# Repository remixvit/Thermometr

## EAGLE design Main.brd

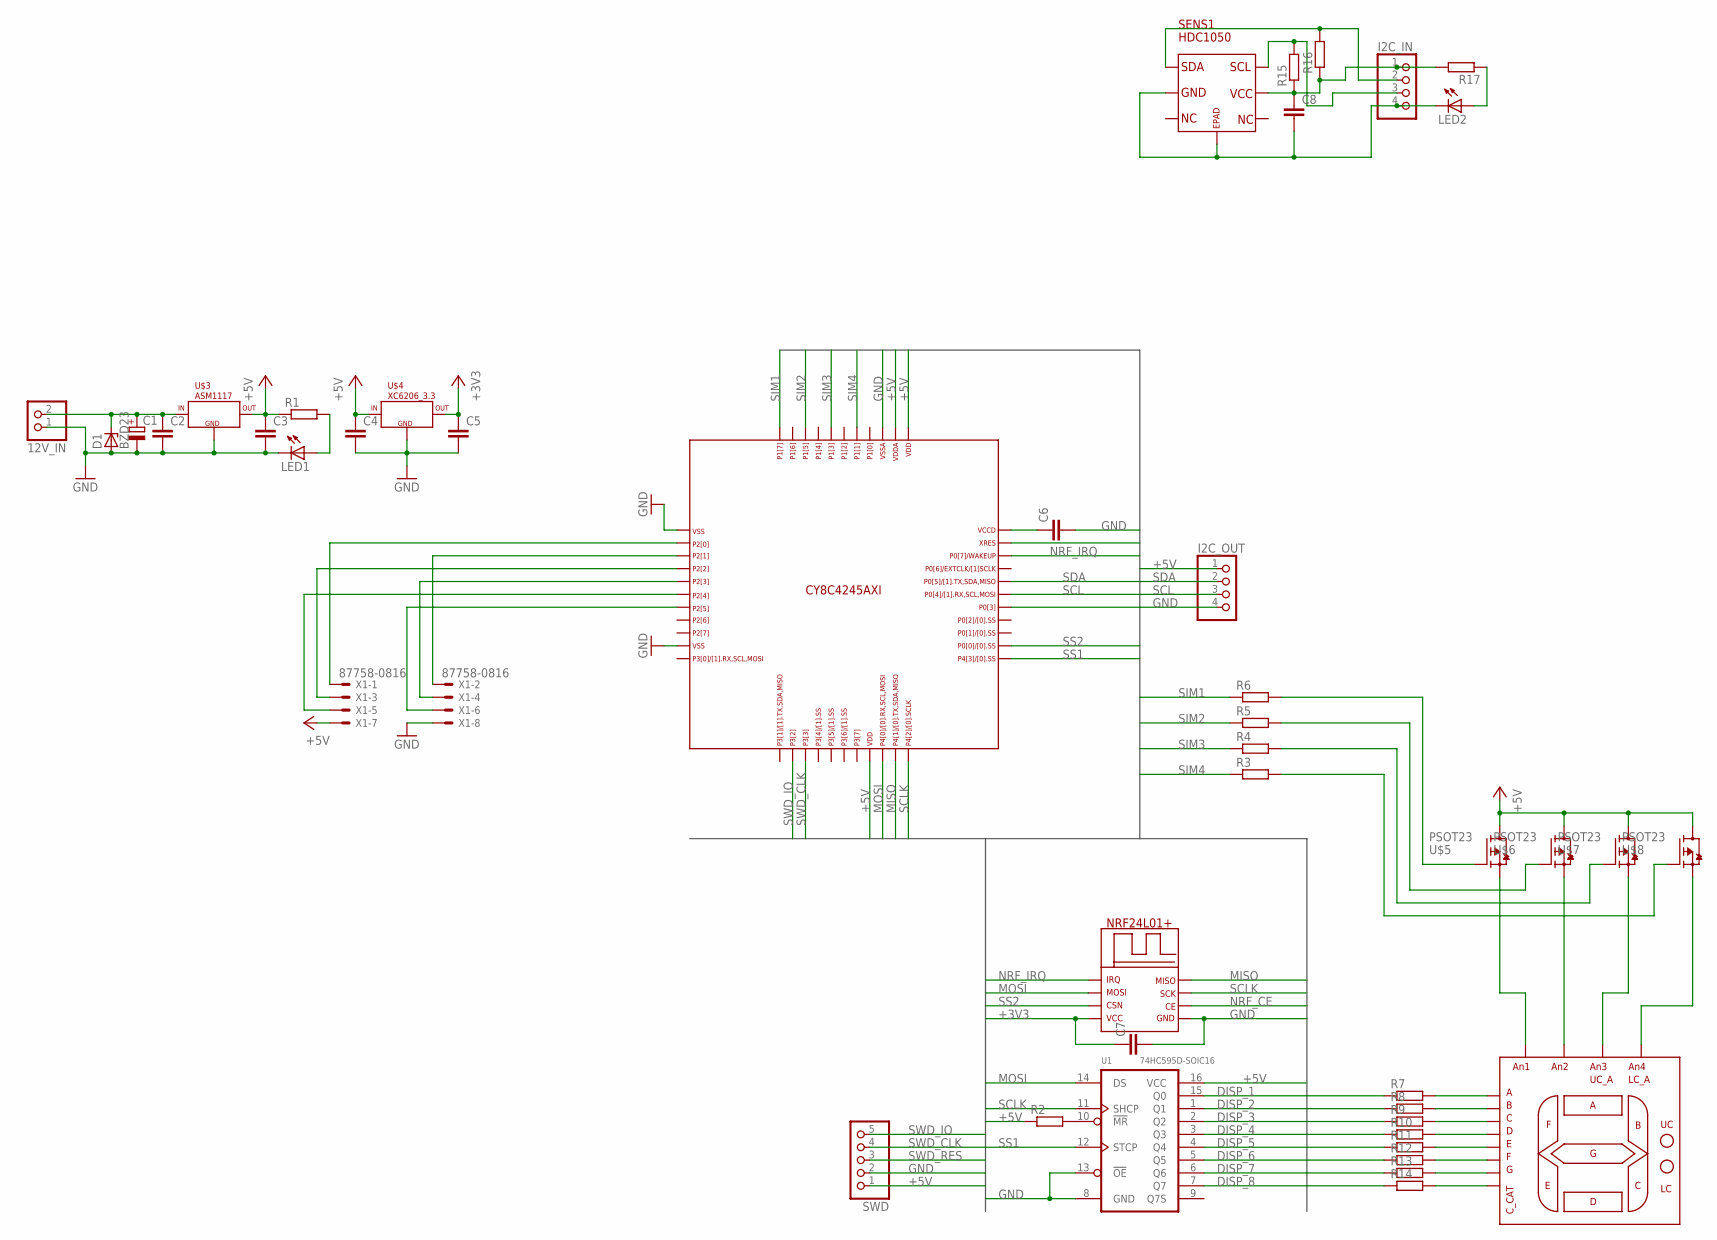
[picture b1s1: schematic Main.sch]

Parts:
12V_IN: PINHD-1X2; 1X02
C1: CPOL-EU150CLZ-0810; 150CLZ-0810
C2, C3, C4, C5, C6, C7, C8: C-EUC0805; C0805
D1: BZD23; SOD81
DISPLAY1: 4DIGIT_7SEG; 4DIG_7SEG_5.3X19
I2C_IN, I2C_OUT: PINHD-1X4; 1X04
LED1, LED2: LEDCHIP-LED0805; CHIP-LED0805
R1, R2, R3, R4, R5, R6, R7, R8, R9, R10, R11, R12, R13, R14, R15, R16, R17: R-EU_M0805; M0805
SENS1: HDC1050; PWSON6
SWD: PINHD-1X5; 1X05
U1: 74HC595D-SOIC16; SOIC16-1.27-10X3.9MM
U$1: CY8C4245; TQFP44_CY_LOGO
U$2: NRF24; NRF
U$3: ASM1117; SOT223
U$4: XC6206_3.3; SOT23
U$5, U$6, U$7, U$8: PSOT23; SOT23
X1: 87758-0816

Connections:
+3V3: C5.1, C7.1, U$2.VCC, U$4.2 (OUT)
+5V: C3.1, C4.1, I2C_OUT.1, R1.1, R2.1, SWD.1, U1.16 (VCC), U$1.19, U$1.34, U$1.35, U$3.2 (OUT), U$3.4 (OUT), U$4.3 (IN), U$5.S, U$6.S, U$7.S, U$8.S, X1.7
DISP_1: R7.1, U1.15 (Q0)
DISP_2: R8.1, U1.1 (Q1)
DISP_3: R9.1, U1.2 (Q2)
DISP_4: R10.1, U1.3 (Q3)
DISP_5: R11.1, U1.4 (Q4)
DISP_6: R12.1, U1.5 (Q5)
DISP_7: R13.1, U1.6 (Q6)
DISP_8: R14.1, U1.7 (Q7)
GND: 12V_IN.1, C1.-, C2.2, C3.2, C4.2, C5.2, C6.2, C7.2, D1.A, I2C_OUT.4, LED1.C, SWD.2, U1.8 (GND), U1.13 (!OE), U$1.1, U$1.10, U$1.36, U$2.GND, U$3.1 (GND), U$4.1 (GND), X1.8
MISO: U$1.21, U$2.MISO
MOSI: U1.14 (DS), U$1.20, U$2.MOSI
unnamed: 12V_IN.2, C1.+, C2.1, D1.C, U$3.3 (IN)
unnamed: R2.2, U1.10 (!MR)
unnamed: LED1.A, R1.2
unnamed: C8.1, I2C_IN.1, R15.1, R16.1, R17.2, SENS1.P$5
unnamed: C8.2, I2C_IN.4, LED2.C, SENS1.EPAD, SENS1.P$2
unnamed: I2C_IN.2, R16.2, SENS1.P$1
unnamed: I2C_IN.3, R15.2, SENS1.P$6
unnamed: C6.1, U$1.33
unnamed: DISPLAY1.12, U$5.D
unnamed: DISPLAY1.9, U$6.D
unnamed: DISPLAY1.8, U$7.D
unnamed: DISPLAY1.6, U$8.D
unnamed: R3.2, U$8.G
unnamed: DISPLAY1.11, R7.2
unnamed: R4.2, U$7.G
unnamed: R5.2, U$6.G
unnamed: R6.2, U$5.G
unnamed: DISPLAY1.7, R8.2
unnamed: DISPLAY1.4, R9.2
unnamed: DISPLAY1.2, R10.2
unnamed: DISPLAY1.1, R11.2
unnamed: DISPLAY1.10, R12.2
unnamed: DISPLAY1.5, R13.2
unnamed: DISPLAY1.3, R14.2
unnamed: U$1.2, X1.1
unnamed: U$1.3, X1.2
unnamed: U$1.4, X1.3
unnamed: U$1.5, X1.4
unnamed: U$1.6, X1.5
unnamed: U$1.7, X1.6
unnamed: LED2.A, R17.1
NRF_CE: U$1.27, U$2.CE
NRF_IRQ: U$1.31, U$2.IRQ
SCL: I2C_OUT.3, U$1.28
SCLK: U1.11 (SHCP), U$1.22, U$2.SCK
SDA: I2C_OUT.2, U$1.29
SIM1: R6.1, U$1.44
SIM2: R5.1, U$1.42
SIM3: R4.1, U$1.40
SIM4: R3.1, U$1.38
SS1: U1.12 (STCP), U$1.23
SS2: U$1.24, U$2.CSN
SWD_CLK: SWD.4, U$1.14
SWD_IO: SWD.5, U$1.13
SWD_RES: SWD.3, U$1.32

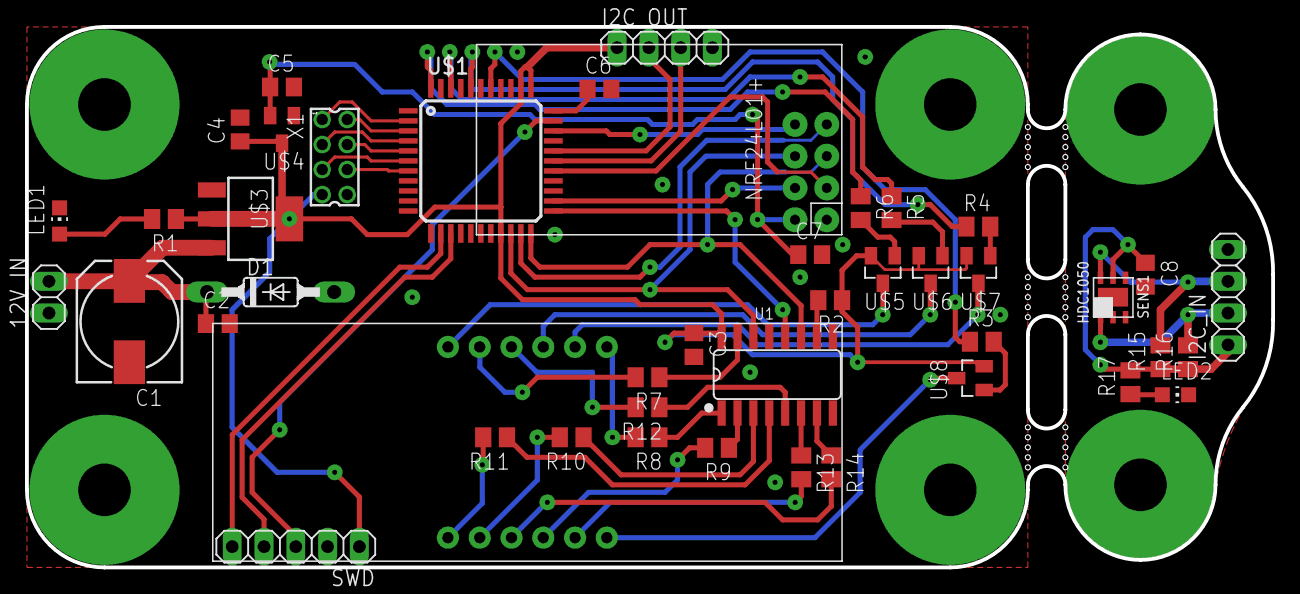
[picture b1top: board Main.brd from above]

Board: 2 copper layers, 99.6 x 43.2 mm, 44 parts (0 on the bottom side), 58 nets.

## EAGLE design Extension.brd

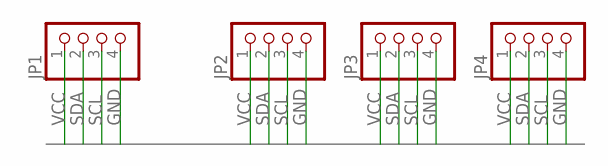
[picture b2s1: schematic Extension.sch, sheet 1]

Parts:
JP1, JP2, JP3, JP4: PINHD-1X4; 1X04

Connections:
GND: JP1.4, JP2.4, JP3.4, JP4.4
SCL: JP1.3, JP2.3, JP3.3, JP4.3
SDA: JP1.2, JP2.2, JP3.2, JP4.2
VCC: JP1.1, JP2.1, JP3.1, JP4.1

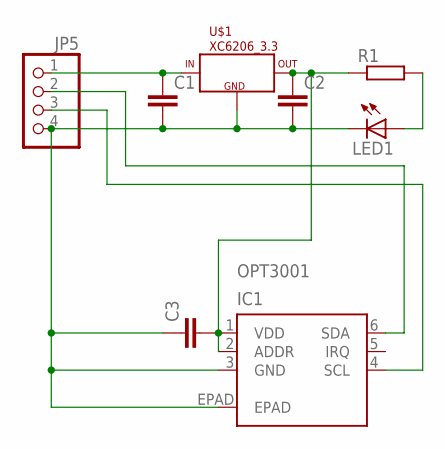
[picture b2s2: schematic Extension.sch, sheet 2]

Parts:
C1, C2, C3: C-EUC0805; C0805
IC1: OPT3001; USON6
JP5: PINHD-1X4; 1X04
LED1: LEDCHIPLED_0805; CHIPLED_0805
R1: R-EU_R0805; R0805
U$1: XC6206_3.3; SOT23

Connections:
unnamed: C1.1, JP5.1, U$1.3 (IN)
unnamed: C1.2, C2.2, C3.1, IC1.3 (GND), IC1.EPAD, JP5.4, LED1.C, U$1.1 (GND)
unnamed: C2.1, C3.2, IC1.1 (VDD), IC1.2 (ADDR), R1.1, U$1.2 (OUT)
unnamed: IC1.6 (SDA), JP5.2
unnamed: IC1.4 (SCL), JP5.3
unnamed: LED1.A, R1.2

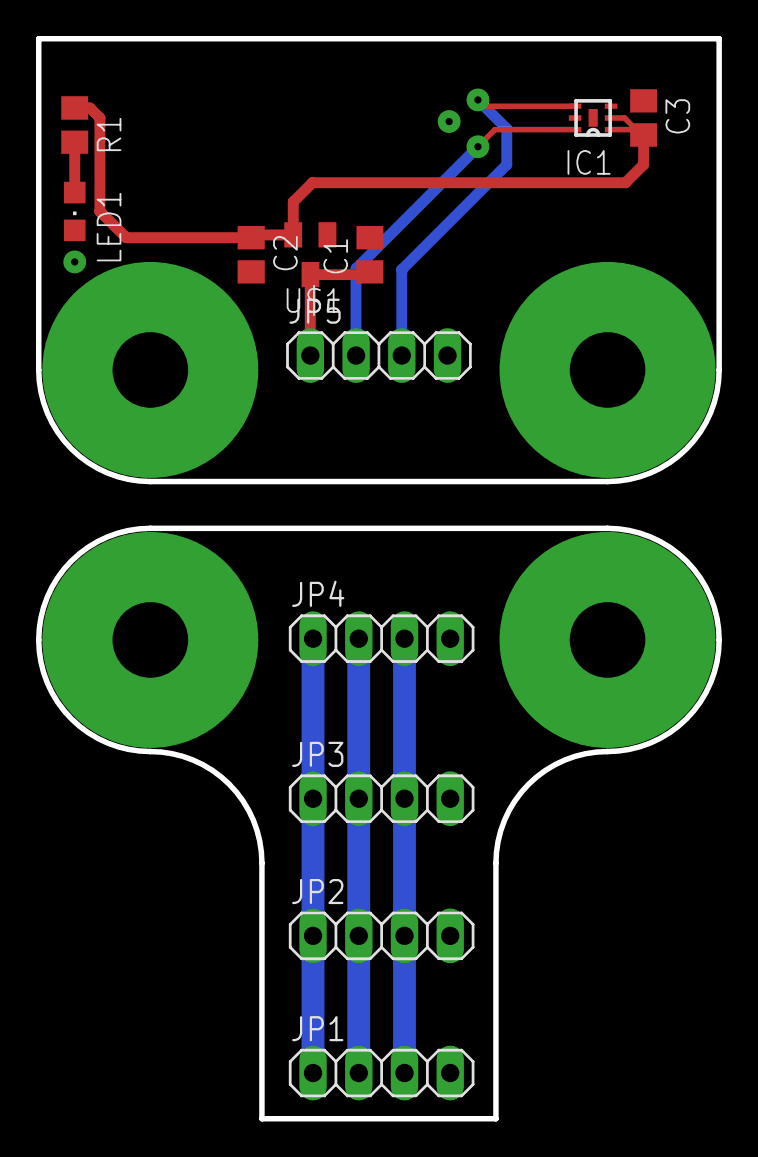
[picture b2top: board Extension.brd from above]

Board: 2 copper layers, 37.8 x 60.0 mm, 12 parts (0 on the bottom side), 10 nets.

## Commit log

2016-01-14 Create shematic
2016-01-14 Route PCB
2016-01-18 BugFix
2016-01-26 Add Firmware
2016-02-08 Remove frame bufer
